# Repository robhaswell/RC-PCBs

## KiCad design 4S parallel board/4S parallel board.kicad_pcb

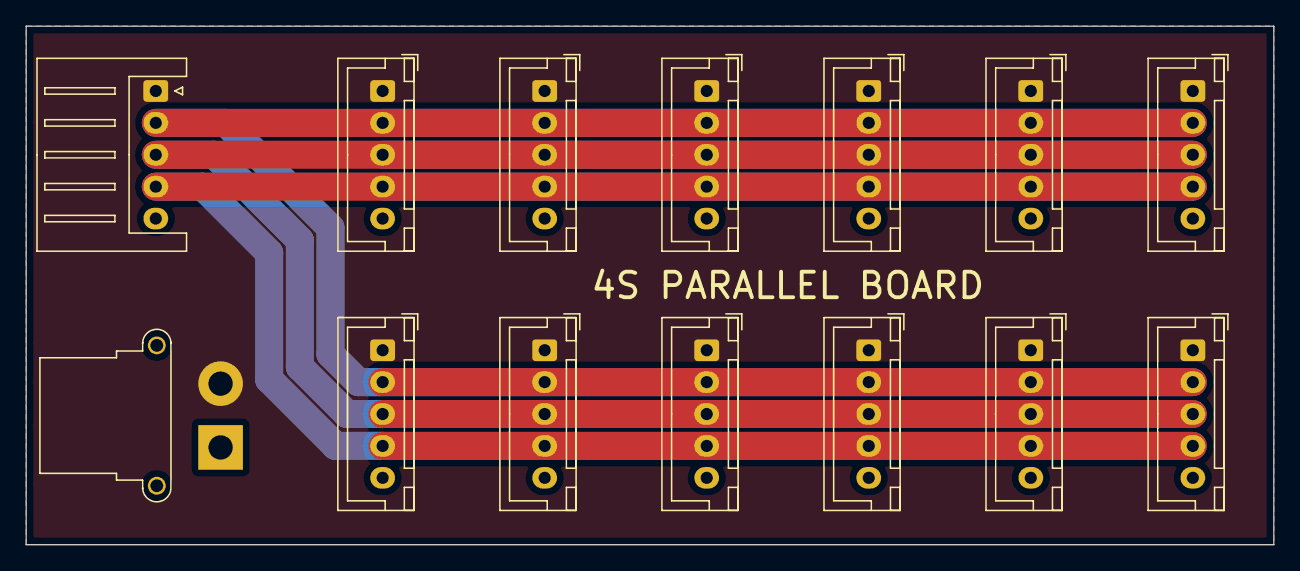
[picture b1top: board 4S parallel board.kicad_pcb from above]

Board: 2 copper layers, 97.8 x 40.6 mm, 14 parts (0 on the bottom side), 5 nets.

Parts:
J1: Conn_01x02; AMASS_XT30PW-F_1x02_P2.50mm_Horizontal
J2: Conn_01x05; JST_XH_S5B-XH-A_1x05_P2.50mm_Horizontal
J3, J4, J5, J6, J7, J8, J9, J10, J11, J12, J13, J14: Conn_01x05; JST_XH_B5B-XH-A_1x05_P2.50mm_Vertical

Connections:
/B2: J2.2, J3.2, J4.2, J5.2, J6.2, J7.2, J8.2, J9.2, J10.2, J11.2, J12.2, J13.2, J14.2
/B3: J2.3, J3.3, J4.3, J5.3, J6.3, J7.3, J8.3, J9.3, J10.3, J11.3, J12.3, J13.3, J14.3
/B4: J2.4, J3.4, J4.4, J5.4, J6.4, J7.4, J8.4, J9.4, J10.4, J11.4, J12.4, J13.4, J14.4
GND: J1.1, J2.5, J3.5, J4.5, J5.5, J6.5, J7.5, J8.5, J9.5, J10.5, J11.5, J12.5, J13.5, J14.5
VCC: J1.2, J2.1, J3.1, J4.1, J5.1, J6.1, J7.1, J8.1, J9.1, J10.1, J11.1, J12.1, J13.1, J14.1

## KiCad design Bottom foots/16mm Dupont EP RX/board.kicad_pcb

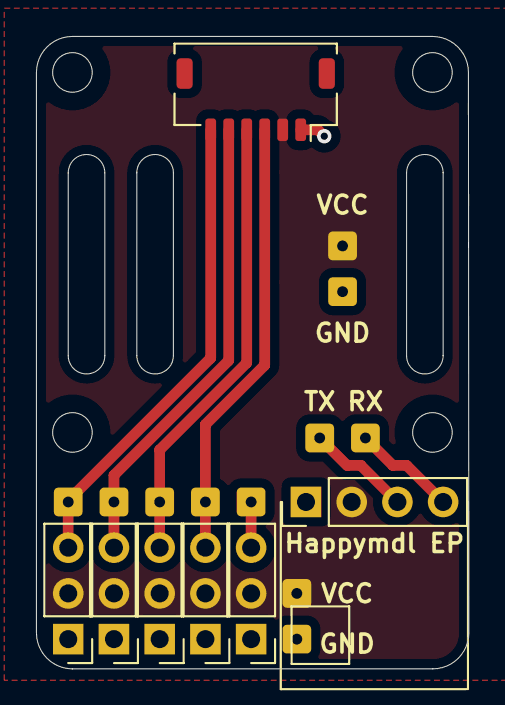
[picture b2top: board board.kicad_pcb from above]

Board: 2 copper layers, 24.0 x 35.1 mm, 21 parts (0 on the bottom side), 7 nets.

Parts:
H1, H2, H3, H4: MountingHole; MountingHole_2.2mm_M2
J1: Conn_01x06; JST_SHL_SM06B-SHLS-TF_1x06-1MP_P1.00mm_Horizontal
J2, J3, J4, J5, J11: Conn_01x03; PinHeader_1x03_P2.54mm_Vertical
J6, J6#2, J7, J8, J9, J10, J10#2, J12, J12#2, J12#3, J13: Conn_01x01; SolderWire-0.1sqmm_1x01_D0.4mm_OD1mm

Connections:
+BATT: J1.2, J2.2, J3.2, J4.2, J5.2, J10.1, J10#2.1, J11.2
GND: J1.1, J2.1, J3.1, J4.1, J5.1, J6.1, J6#2.1, J11.1
unnamed: J1.3, J5.3, J9.1
unnamed: J1.4, J4.3, J8.1
unnamed: J1.5, J3.3, J7.1
unnamed: J1.6, J2.3, J13.1
unnamed: J11.3, J12#3.1

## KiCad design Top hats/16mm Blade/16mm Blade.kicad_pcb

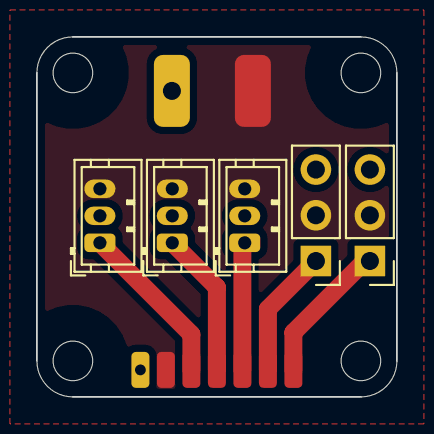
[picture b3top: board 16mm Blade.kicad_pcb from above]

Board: 2 copper layers, 20.0 x 20.0 mm, 18 parts (0 on the bottom side), 7 nets.

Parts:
H1, H2, H3, H4: MountingHole; MountingHole_2.2mm_M2
J1, J2, J3, J4, J5, J6, J7: Conn_01x01; SolderWirePad_1x01_SMD_1x2mm
J8, J9: Conn_01x01; SolderWirePad_1x01_SMD_2x4mm
J10, J11, J12: Conn_01x03; JST_ZH_B3B-ZR_1x03_P1.50mm_Vertical
J13, J14: Conn_01x03; PinHeader_1x03_P2.54mm_Vertical

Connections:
GND: J1.1, J8.1, J10.2, J11.2, J12.2, J13.3, J14.3
unnamed: J3.1, J10.1
unnamed: J4.1, J11.1
unnamed: J5.1, J12.1
unnamed: J6.1, J13.1
unnamed: J7.1, J14.1
VCC: J2.1, J9.1, J10.3, J11.3, J12.3, J13.2, J14.2
